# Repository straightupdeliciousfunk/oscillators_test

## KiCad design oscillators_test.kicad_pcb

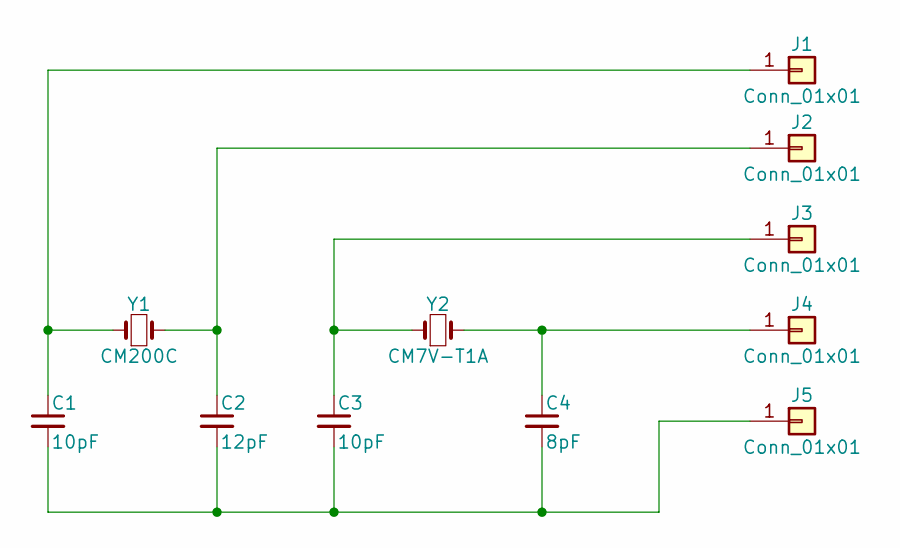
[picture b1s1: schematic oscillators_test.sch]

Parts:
C1, C3: 10pF; C_1206_HandSoldering
C2: 12pF; C_1206_HandSoldering
C4: 8pF; C_1206_HandSoldering
J1, J2, J3, J4, J5: Conn_01x01; Pin_Header_Straight_1x01_Pitch2.54mm
Y1: CM200C
Y2: CM7V-T1A

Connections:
unnamed: C1.1, J1.1, Y1.1
unnamed: C1.2, C2.2, C3.2, C4.2, J5.1
unnamed: C2.1, J2.1, Y1.2
unnamed: C3.1, J3.1, Y2.1
unnamed: C4.1, J4.1, Y2.2

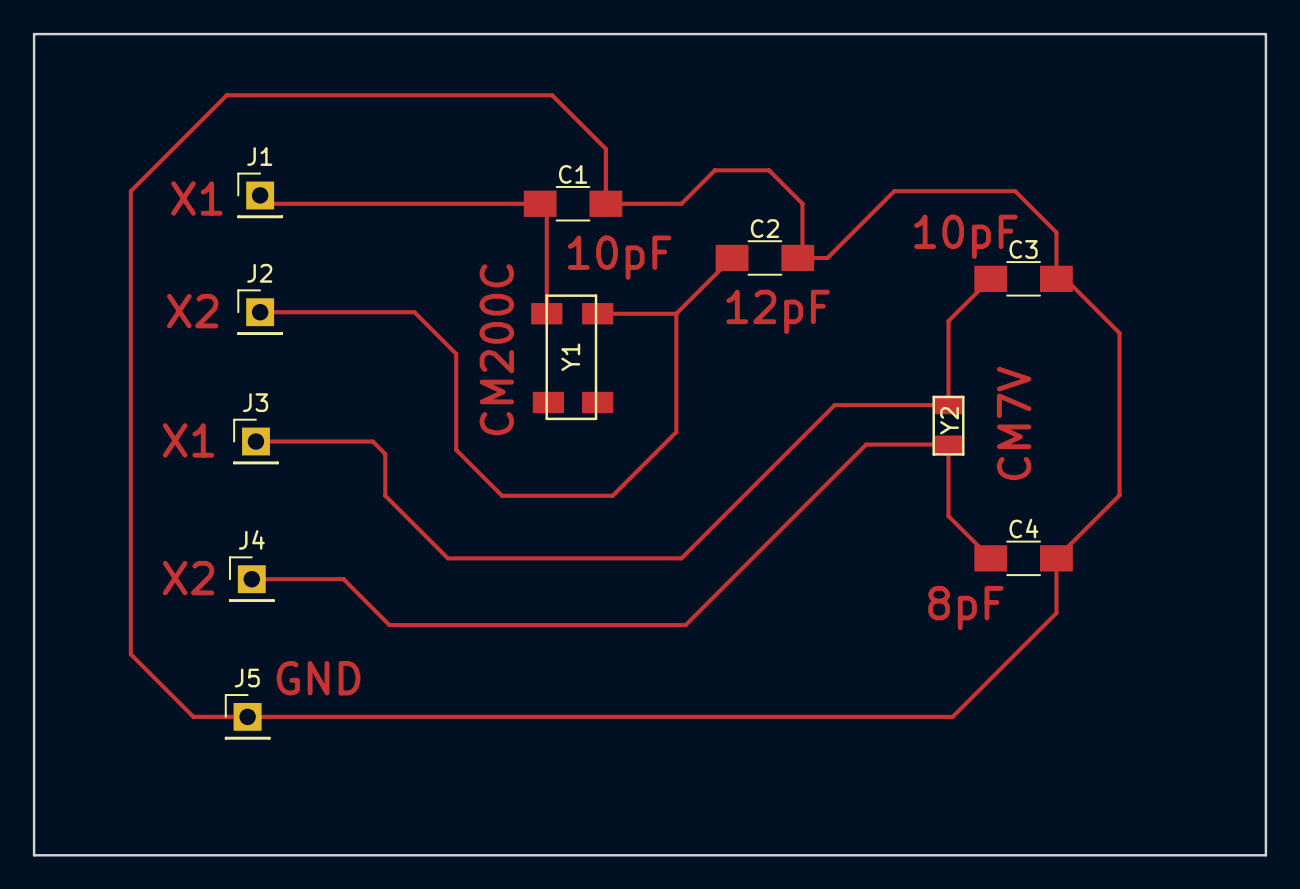
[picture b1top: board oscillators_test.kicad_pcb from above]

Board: 2 copper layers, 75.0 x 50.0 mm, 11 parts (0 on the bottom side), 5 nets.

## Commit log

2018-04-27 initial commit
    quick breakout board for a CM200C and a CM7V (both 38kHz oscillators)
